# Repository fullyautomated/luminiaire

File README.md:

# Luminiaire

Small, efficient and cost-effective lights for small scale vertical farming and horticulture research.

## LED boards

The LED boards mount on a 100mm extruded aluminium heatsink (e.g. [SK 81](https://www.fischerelektronik.de/web_fischer/en_GB/heatsinks/A01/Standard%20extruded%20heatsinks/$catalogue/fischerData/PR/SK81_/search.xhtml) or [SK 92](https://www.fischerelektronik.de/web_fischer/en_GB/heatsinks/A01/Standard%20extruded%20heatsinks/$catalogue/fischerData/PG/SK92/search.xhtml)).

## Controller

TODO

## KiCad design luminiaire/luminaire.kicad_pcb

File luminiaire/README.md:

on time: 210ns

OSLON Square, OSLON SSL, OSCONIQ P 3030
OSCONIQ S, DURIS S
OSCONIQ P 2226

https://www.osram.com/appsn/ProductSelector/?refinementList%5B1_app%5D%5B0%5D=Agriculture&page=2

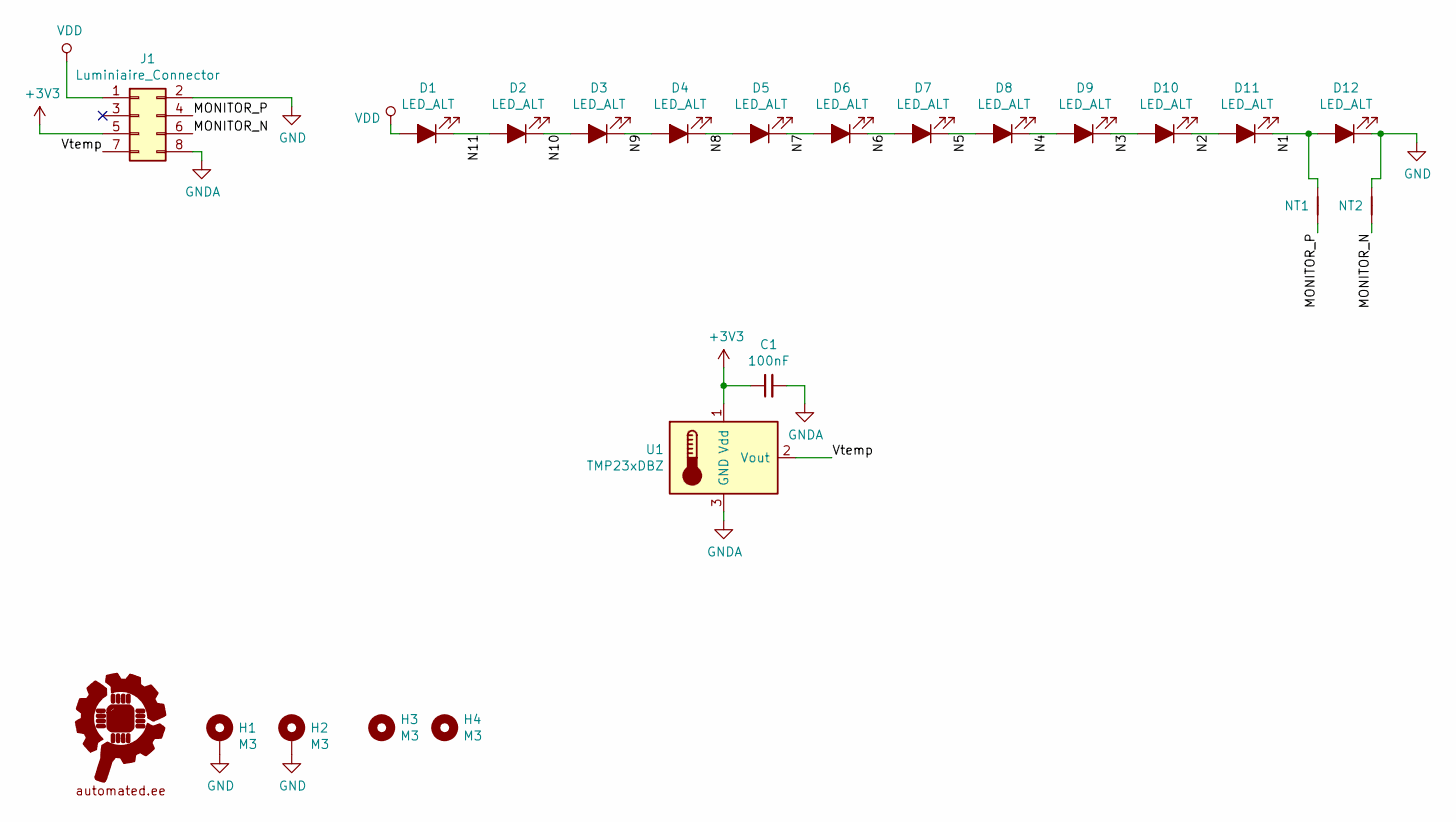
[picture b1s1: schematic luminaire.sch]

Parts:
C1: 100nF; C_0603_1608Metric
D1, D2, D3, D4, D5, D6, D7, D8, D9, D10, D11, D12: LED_ALT; LED_Osram_DURIS_S5_3x2.55x0.6mm
G1: Fully_Automated_Logo; falogo_small_copper
H1, H2: M3; MountingHole_3.2mm_M3_Pad
H3, H4: M3; MountingHole_3.2mm_M3_ISO14580_Pad
J1: Luminiaire_Connector; PinHeader_2x04_P2.54mm_Vertical_SMD
NT1: MONITOR_P; NetTie-2_SMD_Pad0.5mm
NT2: NONITOR_N; NetTie-2_SMD_Pad0.5mm
U1: TMP23xDBZ; SOT-23

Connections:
+3V3: C1.1, J1.5, U1.1 (Vdd)
/MONITOR_N: J1.6, NT2.2
/MONITOR_P: J1.4, NT1.2
/N1: D11.1 (K), D12.2 (A), NT1.1
/N2: D10.1 (K), D11.2 (A)
/N3: D9.1 (K), D10.2 (A)
/N4: D8.1 (K), D9.2 (A)
/N5: D7.1 (K), D8.2 (A)
/N6: D6.1 (K), D7.2 (A)
/N7: D5.1 (K), D6.2 (A)
/N8: D4.1 (K), D5.2 (A)
/N9: D3.1 (K), D4.2 (A)
/N10: D2.1 (K), D3.2 (A)
/N11: D1.1 (K), D2.2 (A)
/Vtemp: J1.7, U1.2 (Vout)
GND: D12.1 (K), H1.1, H2.1, J1.2, NT2.1
GNDA: C1.2, J1.8, U1.3 (GND)
VDD: D1.2 (A), J1.1

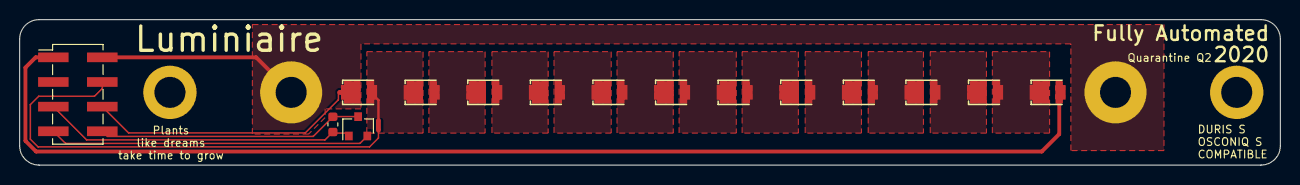
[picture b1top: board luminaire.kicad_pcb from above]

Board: 2 copper layers, 130.0 x 15.0 mm, 22 parts (1 on the bottom side), 18 nets.

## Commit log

2020-08-13 Move luminiaire project into a separate repository
2020-08-13 Add license and move silkscreen away a bit so it doesn't get cut off in production
